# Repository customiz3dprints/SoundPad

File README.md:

# SoundPad

This is a 3 (+1 if you count the rotary encoder) button keypad with media controls and hotkeys (as the F+12 keys) for other apps. The 128x32 OLED screen also displays the current mode (MEDIA-OTHER).

# PCB and Schematic

# Case (The PCB is a layer, between the two parts)

Whole

Top

Bottom

# Firmware
The firmware was written in KMK
- The rotary encoder changes volume, pressing it changes the mode of the keys
- The buttons are: Mode 1 (MEDIA) Previous Track - Play/Pause - Skip track; Mode 2 (OTHER) F13-15

# BOM
2x M3x5mx4mm heatset inserts
2x M316 screws
3x Cherry-MX switxhes with DSA keycaps
1x EC11 rotary encoder
1x 0.91 inch OLED
1x 2 part case (3D printed)

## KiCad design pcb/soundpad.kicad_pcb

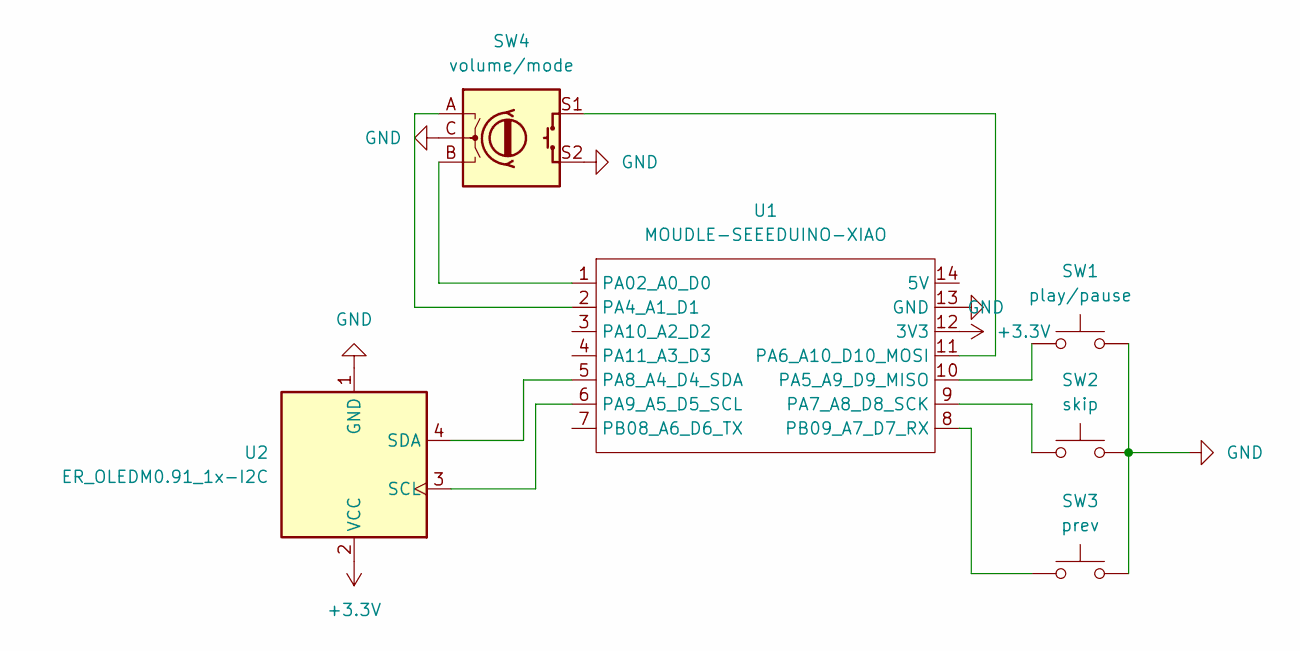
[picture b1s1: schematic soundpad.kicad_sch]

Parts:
SW1: play/pause; SW_Cherry_MX_1.00u_PCB
SW2: skip; SW_Cherry_MX_1.00u_PCB
SW3: prev; SW_Cherry_MX_1.00u_PCB
SW4: volume/mode; RotaryEncoder_Alps_EC11E-Switch_Vertical_H20mm
U1: MOUDLE-SEEEDUINO-XIAO; XIAO-RP2040-DIP
U2: ER_OLEDM0.91_1x-I2C

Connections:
+3.3V: U1.12 (3V3), U2.2 (VCC)
GND: SW1.2, SW2.2, SW3.2, SW4.C, SW4.S2, U1.13 (GND), U2.1 (GND)
unnamed: SW4.B, U1.1 (PA02_A0_D0)
unnamed: SW4.A, U1.2 (PA4_A1_D1)
unnamed: SW1.1, U1.10 (PA5_A9_D9_MISO)
unnamed: SW4.S1, U1.11 (PA6_A10_D10_MOSI)
unnamed: SW2.1, U1.9 (PA7_A8_D8_SCK)
unnamed: U1.5 (PA8_A4_D4_SDA), U2.4 (SDA)
unnamed: U1.6 (PA9_A5_D5_SCL), U2.3 (SCL)
unnamed: SW3.1, U1.8 (PB09_A7_D7_RX)

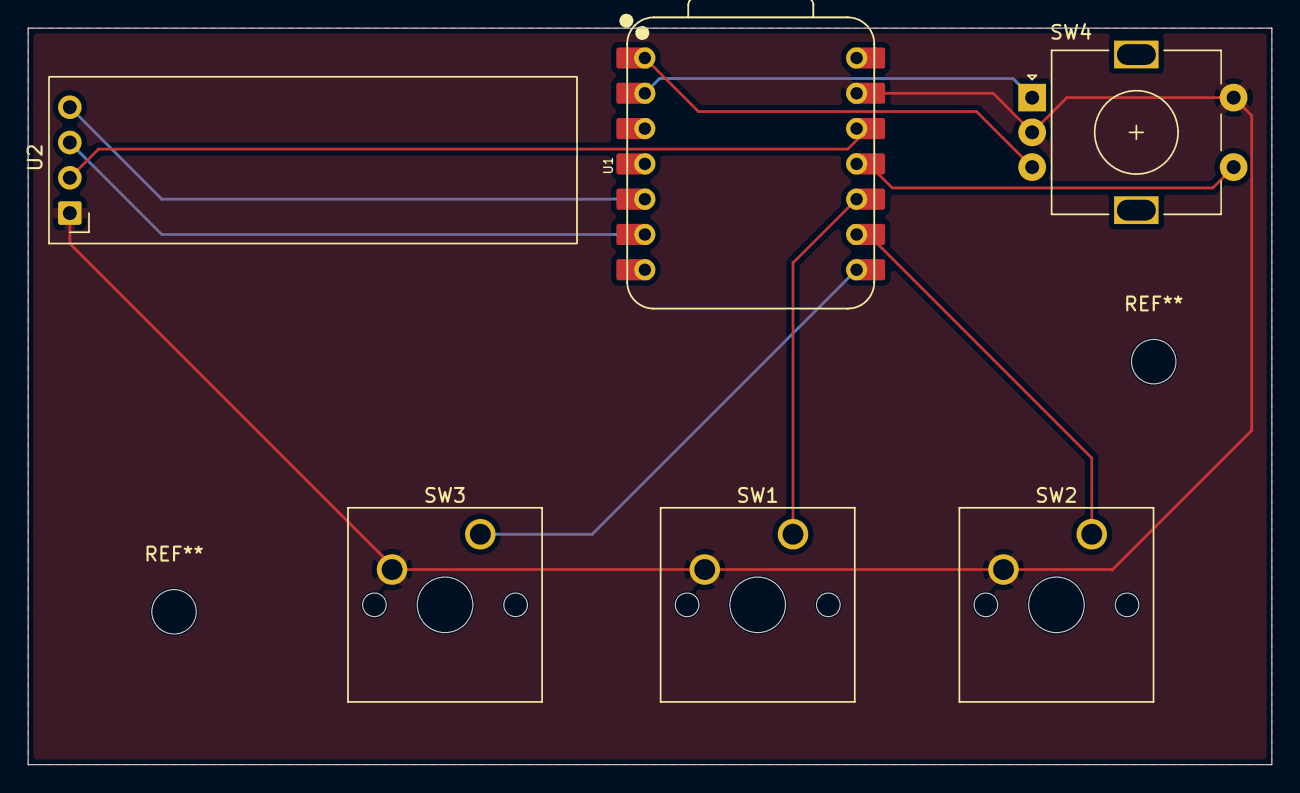
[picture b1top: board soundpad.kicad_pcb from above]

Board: 2 copper layers, 89.5 x 53.0 mm, 6 parts (0 on the bottom side), 10 nets.
